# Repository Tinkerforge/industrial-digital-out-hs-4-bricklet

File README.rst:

Industrial Digital Out HS 4 Bricklet
====================================

**The development of this Bricklet was stopped.**

This repository contains the firmware source code and the hardware design
files. The documentation generator configs can be found at
https://github.com/Tinkerforge/generators

Repository Content
------------------

software/:
 * examples/: Examples for all supported languages
 * build/: Makefile and compiled files
 * src/: Source code of firmware
 * generate_makefile: Shell script to generate Makefile from cmake script

hardware/:
 * Contains kicad project files and additionally schematics as pdf

datasheets/:
 * Contains datasheets for sensors and complex ICs that are used

Hardware
--------

The hardware is designed with the open source EDA Suite KiCad
(http://www.kicad.org). Before you are able to open the files,
you have to install the Tinkerforge kicad-libraries
(https://github.com/Tinkerforge/kicad-libraries). You can either clone
them directly in hardware/ or clone them in a separate folder and
symlink them into hardware/
(ln -s kicad_path/kicad-libraries project_path/hardware). After that you
can open the .pro file in hardware/ with kicad and from there view and
modify the schematics and the PCB layout.

Software
--------

If you want to do your own Brick/Bricklet firmware development we highly
recommend that you use our build environment setup script and read the
tutorial (https://www.tinkerforge.com/en/doc/Tutorials/Tutorial_Build_Environment/Tutorial.html).

To compile the C code we recommend you to install the newest GNU Arm Embedded
Toolchain (https://launchpad.net/gcc-arm-embedded/+download).
You also need to install bricklib2 (https://github.com/Tinkerforge/bricklib2).

You can either clone it directly in software/src/ or clone it in a
separate folder and symlink it into software/src/
(ln -s bricklib_path/bricklib2 project_path/software/src/). Finally make sure to
have CMake installed (http://www.cmake.org/cmake/resources/software.html).

After that you can generate a Makefile from the cmake script with the
generate_makefile shell script (in software/) and build the firmware
by invoking make in software/build/. The firmware (.zbin) can then be found
in software/build/ and uploaded with brickv (click button "Flashing"
on start screen).

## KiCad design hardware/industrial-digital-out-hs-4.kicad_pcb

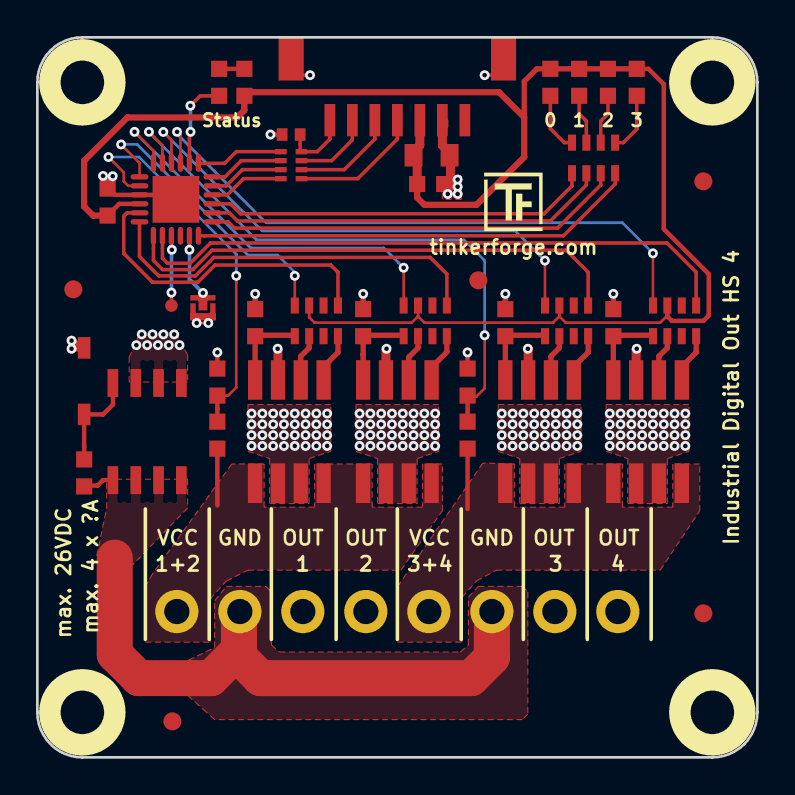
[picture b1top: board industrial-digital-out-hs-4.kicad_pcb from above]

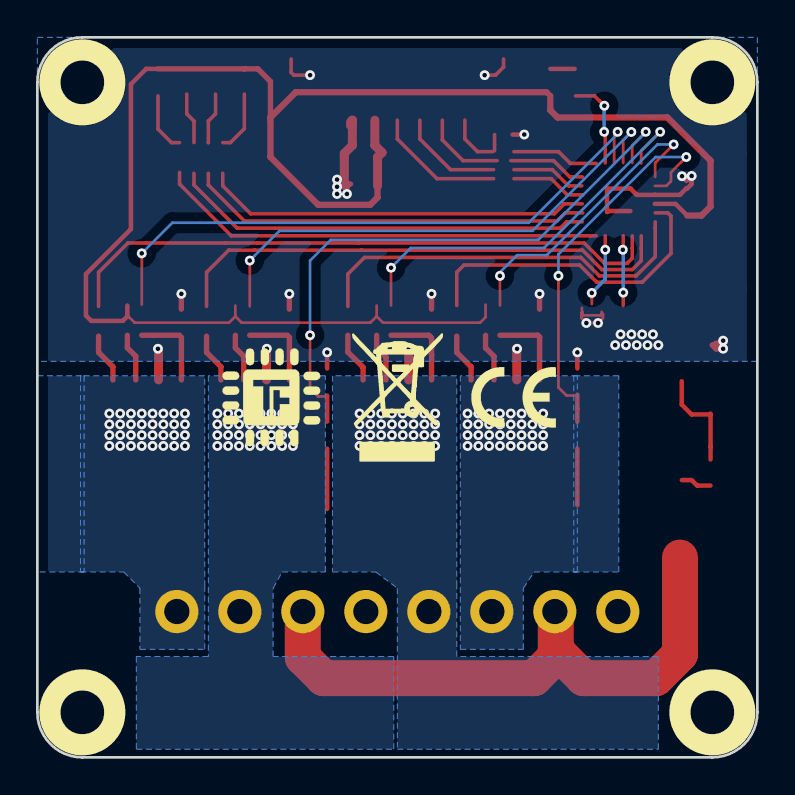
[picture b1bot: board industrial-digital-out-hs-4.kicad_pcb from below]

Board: 2 copper layers, 40.0 x 40.0 mm, 47 parts (2 on the bottom side), 52 nets.

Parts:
C1, C4: 100nF; C0603F
C2: 220pF; C0402F
C3: 10uF; C0805
D1, D2, D3, D4, D5: blue; D0603F
D6: Z12V; SOD-123
Fiducial_Mark: VAL**; Fiducial_Mark
Fiducial_Mark#2, Fiducial_Mark#3, Fiducial_Mark#4, Fiducial_Mark#5: VAL**; Fiducial_Mark
P1: CON-SENSOR; CON-SENSOR2
P2: Digital Output; OQ_8P
P3: Debug; DEBUG_PAD
P4: Boot; SolderJumper
Q1: FDS8449; SOIC-8-MOSFET
R1, R2, R3, R4, R5, R7, R9: 1k; R0603F
R6, R8: 10k; R0603F
R10: 100k; R0603F
RP1, RP4, RP5, RP6: 10k; 4X0603
RP2: 82; 4X0402
RP3: 1k; 0603X4
U1: XMC1100; QFN24-4x4mm-0.5mm
U2, U3, U4, U5: VN7140AS; SO-8
U6, U7, U8, U9: DRILL; DRILL_NP
VAL: WEEE_7mm
VAL#2: CE_5mm

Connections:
3V3: C1.1, C3.1, C4.1, D1.1, D2.1, D3.1, D4.1, D5.1, P1.3, RP1.2, RP4.2, RP5.2, RP6.2, U1.10
GND: C1.2, C2.2, C3.2, C4.2, D6.1, P1.2, P1.EP, P4.1, Q1.S, R1.2, R2.2, R3.2, R4.2, R7.2, R9.2, U1.9, U1.EXP, U2.3, U3.3, U4.3, U5.3
LED0: RP3.1, U1.21
LED1: RP3.2, U1.20
LED2: RP3.3, U1.19
LED3: RP3.4, U1.18
MSense0: RP6.1, U1.7
MSense1: RP5.1, U1.6
MSense2: RP4.1, U1.4
MSense3: RP1.1, U1.3
unnamed: C2.1, P1.7, RP2.4
unnamed: D1.2, R5.2
unnamed: D2.2, RP3.8
unnamed: D3.2, RP3.7
unnamed: D4.2, RP3.6
unnamed: D5.2, RP3.5
unnamed: D6.2, Q1.G, R10.2
unnamed: P1.4, RP2.1
unnamed: P1.5, RP2.2
unnamed: P1.6, RP2.3
unnamed: P2.1, R8.1, U4.5, U4.8, U5.5, U5.8
unnamed: P2.2, P2.6, Q1.D, R10.1
unnamed: P2.3, U5.6, U5.7
unnamed: P2.4, U4.6, U4.7
unnamed: P2.5, R6.1, U2.5, U2.8, U3.5, U3.8
unnamed: P2.7, U3.6, U3.7
unnamed: P2.8, U2.6, U2.7
unnamed: P3.1, U1.15
unnamed: P4.2, U1.17
unnamed: R1.1, RP1.8, U2.4
unnamed: R2.1, RP4.8, U3.4
unnamed: R3.1, RP5.8, U4.4
unnamed: R4.1, RP6.8, U5.4
unnamed: R5.1, U1.2
unnamed: RP1.5, U2.1
unnamed: RP1.7, U2.2
unnamed: RP4.5, U3.1
unnamed: RP4.7, U3.2
unnamed: RP5.5, U4.1
unnamed: RP5.7, U4.2
unnamed: RP6.5, U5.1
unnamed: RP6.7, U5.2
OUT0: RP6.4, U1.11
OUT1: RP5.4, U1.12
OUT2: RP4.4, U1.13
OUT3: RP1.4, U1.14
S-CLK: RP2.7, U1.23
S-CS: RP2.8, U1.22
S-MISO: RP2.5, U1.1
S-MOSI: RP2.6, U1.24
VSense0: R8.2, R9.1, U1.8
VSense1: R6.2, R7.1, U1.5

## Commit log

2019-02-19 Add .gitignore
2019-02-28 added schematic
2019-02-28 first pcb powerside layout
2019-03-01 updated pcb design
2019-03-01 first finished prototype design
2019-03-01 drc check
2019-03-19 Add initial version of firmware
    This is mostly copied from Industrial Digital Out 4 Bricklet 2.0 with
    additional support for CN7140AJ ADC measurements.
2019-03-21 changed out pins to enable pwm, changed pcb design, plotted gerber files for prototype
2019-05-07 Properly abort monoflop on set-(selected-)value call
    Don't clear time on monoflop done/abort to match documentation.
2019-12-02 Mark development as stopped
2021-10-25 Update KiCad link
    https://www.kicad.org/blog/2021/10/Avoid-links-to-former-kicad-domain/
2022-07-06 Add license files.
